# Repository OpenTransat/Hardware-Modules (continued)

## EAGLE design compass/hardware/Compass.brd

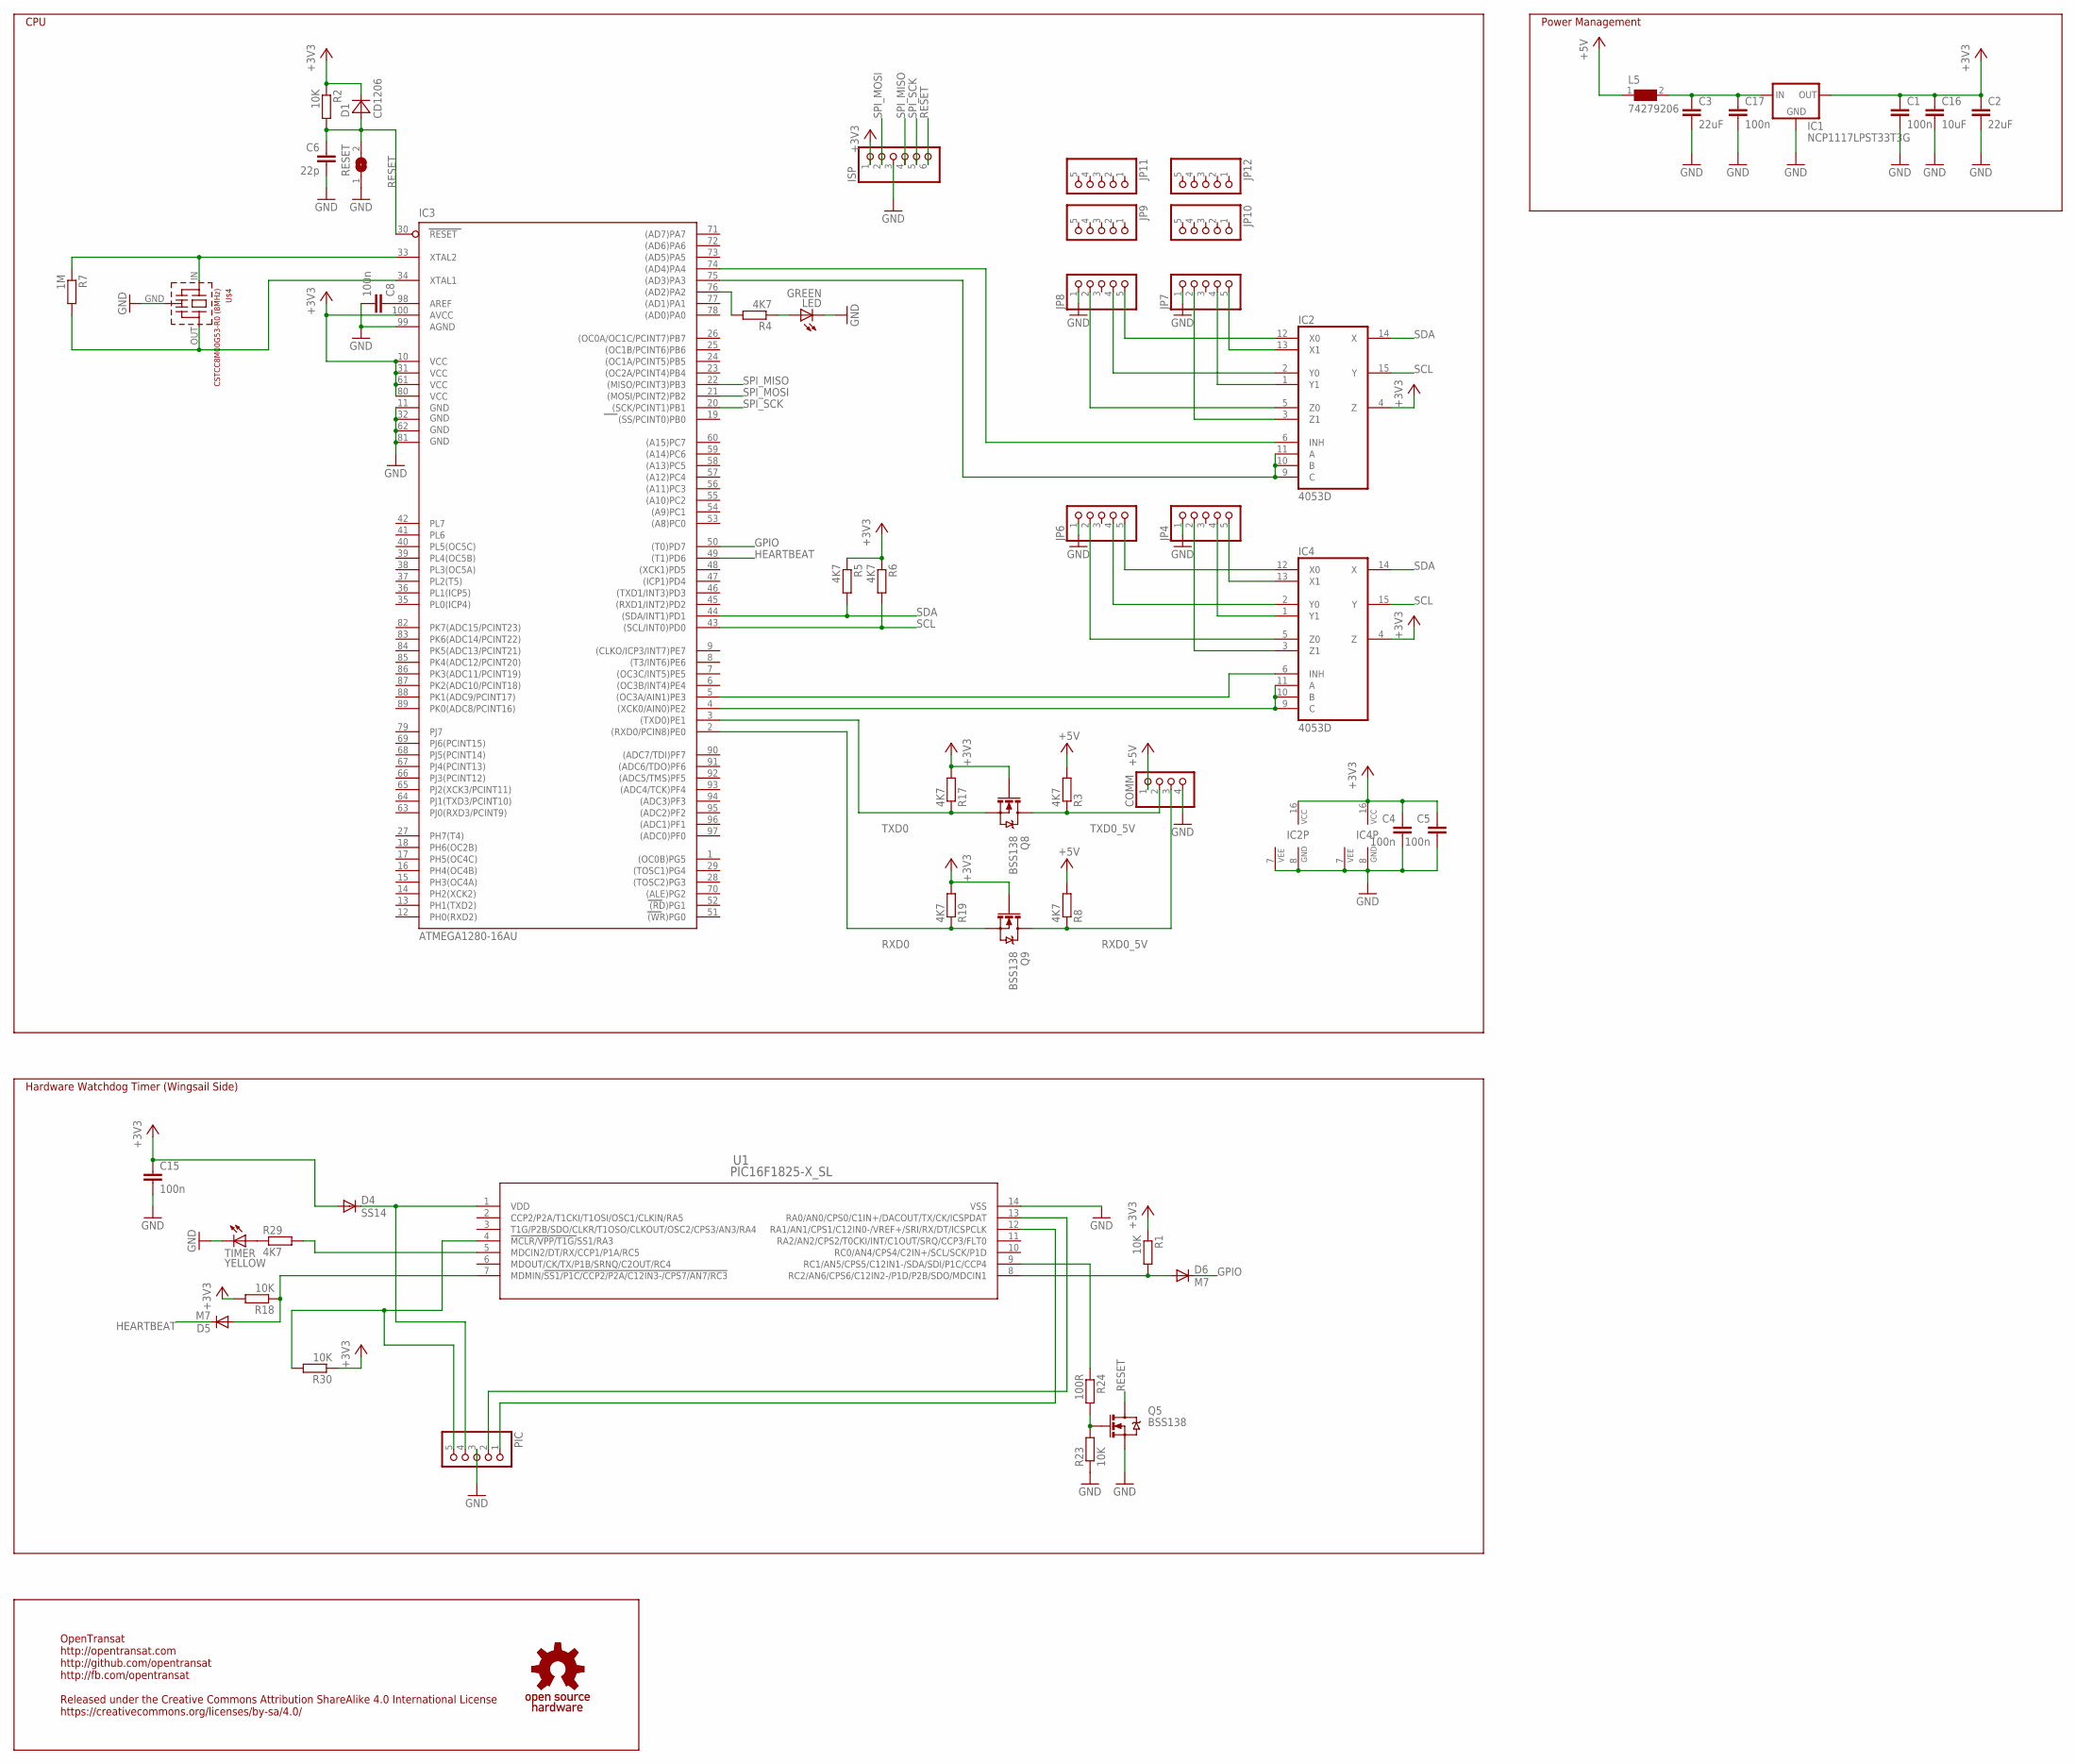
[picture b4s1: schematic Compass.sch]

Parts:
C1, C4, C5, C8, C15, C17: 100n; C0603
C2, C3: 22uF; C1210
C6: 22p; C0603
C16: 10uF; C1206
COMM: PINHD-1X4/90; 1X04/90
D1: CD1206; R1206
D4: SS14; DO214AC
D5, D6: M7; DO-214AC
IC1: NCP1117LPST33T3G; SOT223
IC2, IC4: 4053D; SO16
IC3: ATMEGA1280-16AU; TQFP100
ISP: PINHD-1X6/90; 1X06/90
JP4, JP6, JP7, JP8, JP9, JP10, JP11, JP12: PINHD-1X5; 1X05
L5: 74279206; 0805
LED: GREEN; CHIPLED_0805
PIC: PINHD-1X5/90; 1X05/90
Q5, Q8, Q9: BSS138; SOT23-3
R1, R2, R18, R23, R30: 10K; R0603
R3, R4, R5, R6, R8, R17, R19, R29: 4K7; R0603
R7: 1M; R0603
R24: 100R; R0603
RESET: SJW
TIMER: YELLOW; CHIPLED_0805
U1: PIC16F1825-X_SL; SOIC14-N_MC
U$1: OSHW_S; OSHWS
U$4: CSTCC8M00G53-R0 (8MHz); CSTCC

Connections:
+3V3: C1.1, C2.1, C4.1, C5.1, C15.1, C16.1, D1.2 (C), D4.A, IC1.2 (OUT), IC1.4 (OUT), IC2.4 (Z), IC2.16 (VCC), IC3.10 (VCC), IC3.31 (VCC1), IC3.61 (VCC2), IC3.80 (VCC3), IC3.100 (AVCC), IC4.4 (Z), IC4.16 (VCC), ISP.1, Q8.1 (G), Q9.1 (G), R1.1, R2.1, R5.1, R6.1, R17.2, R18.2, R19.2, R30.1
+5V: COMM.1, L5.1, R3.2, R8.2
GND: C1.2, C2.2, C3.2, C4.2, C5.2, C6.2, C8.2, C15.2, C16.2, C17.2, COMM.4, IC1.1 (GND), IC2.7 (VEE), IC2.8 (GND), IC3.11 (GND), IC3.32 (GND1), IC3.62 (GND2), IC3.81 (GND3), IC3.99 (AGND), IC4.7 (VEE), IC4.8 (GND), ISP.3, JP4.1, JP6.1, JP7.1, JP8.1, LED.C, PIC.3, Q5.2 (S), R23.1, RESET.1, TIMER.C, U1.14 (VSS), U$4.GND
GPIO: D6.C, IC3.50 ((T0)PD7)
HEARTBEAT: D5.C, IC3.49 ((T1)PD6)
unnamed: C3.1, C17.1, IC1.3 (IN), L5.2
unnamed: D6.A, R1.2, U1.8 (RC2/AN6/CPS6/C12IN2-/P1D/P2B/SDO/MDCIN1)
unnamed: C8.1, IC3.98 (AREF)
unnamed: IC4.3 (Z1), JP4.2
unnamed: LED.A, R4.1
unnamed: IC4.1 (Y1), JP4.4
unnamed: IC3.76 ((AD2)PA2), R4.2
unnamed: IC3.4 ((XCK0/AIN0)PE2), IC4.9 (C), IC4.10 (B), IC4.11 (A)
unnamed: IC3.5 ((OC3A/AIN1)PE3), IC4.6 (INH)
unnamed: IC4.13 (X1), JP4.5
unnamed: IC4.12 (X0), JP6.5
unnamed: IC4.2 (Y0), JP6.4
unnamed: IC4.5 (Z0), JP6.2
unnamed: IC2.9 (C), IC2.10 (B), IC2.11 (A), IC3.75 ((AD3)PA3)
unnamed: IC2.6 (INH), IC3.74 ((AD4)PA4)
unnamed: IC2.3 (Z1), JP7.2
unnamed: IC2.1 (Y1), JP7.4
unnamed: IC2.13 (X1), JP7.5
unnamed: IC2.12 (X0), JP8.5
unnamed: IC2.2 (Y0), JP8.4
unnamed: IC2.5 (Z0), JP8.2
unnamed: D5.A, R18.1, U1.7 (MDMIN/!SS1/P1C/CCP2/P2A/C12IN3-/CPS7/AN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)
unnamed: PIC.2, U1.13 (RA0/AN0/CPS0/C1IN+/DACOUT/TX/CK/ICSPDAT)
unnamed: PIC.5, R30.2, U1.4 (!MCLR/VPP/T1G/!SS1/RA3)
unnamed: PIC.1, U1.12 (RA1/AN1/CPS1/C12IN0-/VREF+/SRI/RX/DT/IC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)
unnamed: D4.C, PIC.4, U1.1 (VDD)
unnamed: R24.1, U1.9 (RC1/AN5/CPS5/C12IN1-/SDA/SDI/P1C/CCP4)
unnamed: Q5.1 (G), R23.2, R24.2
unnamed: R29.2, U1.5 (MDCIN2/DT/RX/CCP1/P1A/RC5)
unnamed: R29.1, TIMER.A
RESET: C6.1, D1.1 (A), IC3.30 (RESET), ISP.6, Q5.3 (D), R2.2, RESET.2
RXD0: IC3.2 ((RXD0/PCIN8)PE0), Q9.2 (S), R19.1
RXD0_5V: COMM.3, Q9.3 (D), R8.1
SCL: IC2.15 (Y), IC3.43 ((SCL/INT0)PD0), IC4.15 (Y), R6.2
SDA: IC2.14 (X), IC3.44 ((SDA/INT1)PD1), IC4.14 (X), R5.2
SPI_MISO: IC3.22 ((MISO/PCINT3)PB3), ISP.4
SPI_MOSI: IC3.21 ((MOSI/PCINT2)PB2), ISP.2
SPI_SCK: IC3.20 ((SCK/PCINT1)PB1), ISP.5
TXD0: IC3.3 ((TXD0)PE1), Q8.2 (S), R17.1
TXD0_5V: COMM.2, Q8.3 (D), R3.1
XTAL3: IC3.33 (XTAL2), R7.1, U$4.IN
XTAL4: IC3.34 (XTAL1), R7.2, U$4.OUT

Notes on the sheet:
OpenTransat http://opentransat.com http://github.com/opentransat http://fb.com/opentransat Released under the Creative Commons Attribution ShareAlike 4.0 International License https://creativecommons.org/licenses/by-sa/4.0/
Power Management
CPU
Hardware Watchdog Timer (Wingsail Side)

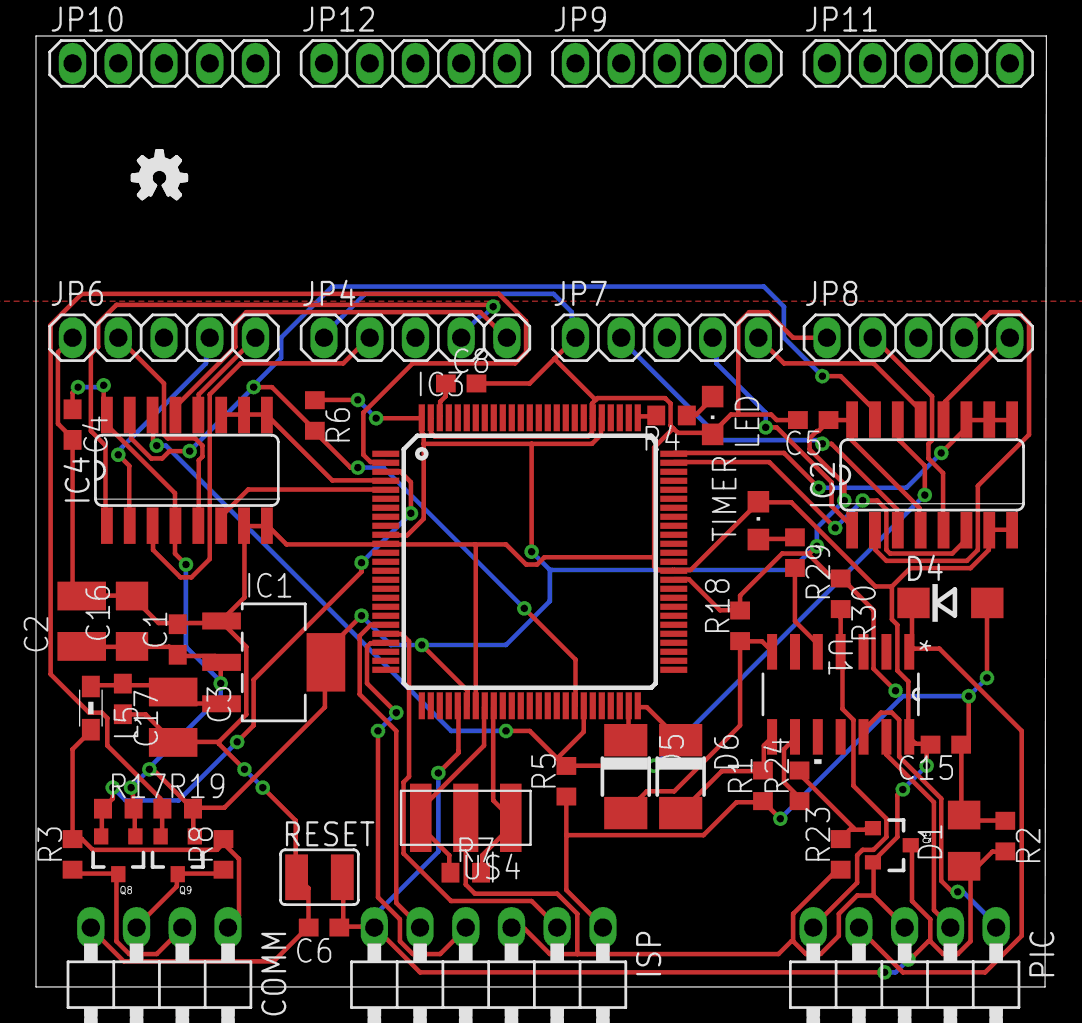
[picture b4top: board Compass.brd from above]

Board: 2 copper layers, 56.1 x 52.8 mm, 54 parts (0 on the bottom side), 47 nets.

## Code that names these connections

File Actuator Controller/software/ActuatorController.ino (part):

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uint8_t buflen = RH_ASK_MAX_MESSAGE_LEN;

//pins
#define LED 13 //PB5
#define HEARTBEAT 6 //PD6
#define IN1 7 //PD7
#define IN2 8 //PB0
#define IN3 9 //PB1
#define IN4 10 //PB2
#define POT A7 //analog input ADC7
#define THERM A0 //analog input PC0,ADC0
#define PWRSENSOR_ON 1 //PD1,TX
#define ACT_ON 0 //PD0,RX (switches EMS & motor driver DC+)
#define RF_TX 3 //PD3
#define RF_RX 2 //PD2
#define RF_TX_ON 5 //PD5
#define RF_RX_ON 4 //PD4
#define ENC_CS A1 //PC1, EMS:6
#define ENC_CLK A3 //PC3, EMS:2
#define ENC_DO A2 //PC2, EMS:4

#define ACT_TIMEOUT 45000UL //number of milliseconds when the actuator is not moving
#define ENC_TRIALS 10 //how many times to read the encoder when parity fails
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void setup() {
  pinMode(LED, OUTPUT);
  digitalWrite(LED, LOW);
  pinMode(HEARTBEAT, OUTPUT);


  #ifdef SERIAL_DEBUG
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  
  pinMode(ACT_ON, OUTPUT);
  digitalWrite(ACT_ON, LOW);
  pinMode(RF_TX_ON, OUTPUT);
  digitalWrite(RF_TX_ON, LOW); //transmitter on only when needed
  pinMode(RF_RX_ON, OUTPUT);
  digitalWrite(RF_RX_ON, LOW);

  ina219.begin(); 
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
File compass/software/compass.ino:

//increase I2C BUFFER to 128 bytes:
//twi.h: TWI_BUFFER_LENGTH 128
//Wire.h: BUFFER_LENGTH 128

#include "Globals.h"
#include <Wire.h>
#include <SPI.h>
#include <EEPROM.h>

#define ROUND(x) ((x)>=0?(int)((x)+0.5):(int)((x)-0.5))
#define RESET() digitalWrite(GPIO, LOW)
#define DELAY_RESET() { delay_sec(4); digitalWrite(GPIO, LOW); }

//#define SERIAL_DEBUG //show command received
//#define DEBUG_COMPASS //uncomment for calibrating
//#define CALIB_COMPASS //uncomment for calibrating

#define DEFAULT_COMPASS 1
#define SERIAL_BAUD 38400 //accepted baud for 8MHz: 9600, 14400, 19200, 38400 https://cache.amobbs.com/bbs_upload782111/files_22/ourdev_508497.html
#define DETECT_CHANGE_EQUAL_MAX 50
#define DETECT_CHANGE_FLOAT_FACTOR 10000

#define LED 24 //PA2
#define MUX1_ABC 70 //PE2
#define MUX1_INH 5 //PE3
#define MUX2_ABC 25 //PA3
#define MUX2_INH 26 //PA4
#define HEARTBEAT 71 //PD6
#define GPIO 38 //PD7

char hb;
bool save_calib = false;

//EEPROM data with checking to store the next waypoint
struct EEPROM_data {
  uint8_t compass_num;
  uint8_t crc;
};
EEPROM_data ee;
#define EEPROM_ADDR 0

void saveEEPROM() {
  ee.crc = ee.compass_num;
  EEPROM.put(EEPROM_ADDR, ee);
}

void loadEEPROM() {
  EEPROM.get(EEPROM_ADDR, ee);
  if (ee.compass_num < 1 || ee.compass_num > 4 || ee.crc != ee.compass_num) {
    ee.compass_num = DEFAULT_COMPASS;
    saveEEPROM();
  }
}

void setCompass(uint8_t x) { //0 = none, 1, 2, 3, 4
  ee.compass_num = x; // global var
  switch (x) {
    case 0:
      digitalWrite(MUX1_INH, HIGH);
      digitalWrite(MUX1_INH, HIGH);
      digitalWrite(MUX1_ABC, LOW);
      digitalWrite(MUX2_ABC, LOW);
      break;
    case 1:
      digitalWrite(MUX2_INH, HIGH);
      digitalWrite(MUX2_ABC, LOW);
      digitalWrite(MUX1_ABC, LOW);
      digitalWrite(MUX1_INH, LOW);
      break;       
    case 2:
      digitalWrite(MUX2_INH, HIGH);
      digitalWrite(MUX2_ABC, LOW);
      digitalWrite(MUX1_ABC, HIGH);    
      digitalWrite(MUX1_INH, LOW);
      break;       
    case 3:
      digitalWrite(MUX1_INH, HIGH);
      digitalWrite(MUX1_ABC, LOW);    
      digitalWrite(MUX2_ABC, HIGH);    
      digitalWrite(MUX2_INH, LOW);
      break;       
    case 4:
      digitalWrite(MUX1_INH, HIGH);
      digitalWrite(MUX1_ABC, LOW);    
      digitalWrite(MUX2_ABC, LOW);    
      digitalWrite(MUX2_INH, LOW);
      break;
    default:
      break;
  }
}

void saveCompass(uint8_t x) {
  ee.compass_num = x;
  saveEEPROM();
}

void setup() {
  //first, all inputs with pullups to minimize power consumption
  DDRA = 0b00000000;
  PORTA = 0b11111111;
  DDRB = 0b00000000;
  PORTB = 0b11111111;
  DDRC = 0b00000000;
  PORTC = 0b11111111;
  DDRD = 0b00000000;
  PORTD = 0b11111111;
  DDRE = 0b00000000;
  PORTE = 0b11111111;
  DDRF = 0b00000000;
  PORTF = 0b11111111;
  DDRG = 0b00000000;
  PORTG = 0b11111111;
  DDRG = 0b00000000;
  PORTG = 0b11111111;
  DDRH = 0b00000000;
  PORTH = 0b11111111;
  DDRJ = 0b00000000;
  PORTJ = 0b11111111;
  DDRK = 0b00000000;
  PORTK = 0b11111111;
  DDRL = 0b00000000;
  PORTL = 0b11111111;
  
  pinMode(MUX1_INH, OUTPUT);
  digitalWrite(MUX1_INH, HIGH); //all compasses turned off by default

  pinMode(MUX2_INH, OUTPUT);
  digitalWrite(MUX2_INH, HIGH); //all compasses turned off by default

  pinMode(MUX1_ABC, OUTPUT);
  pinMode(MUX2_ABC, OUTPUT);

  pinMode(LED, OUTPUT);
  digitalWrite(LED, LOW);

  pinMode(HEARTBEAT, OUTPUT);
  hb = LOW;
  digitalWrite(HEARTBEAT, hb);
  pinMode(GPIO, OUTPUT);
  digitalWrite(GPIO, HIGH);

  Serial.begin(SERIAL_BAUD);
  Serial.println("******************* start *******************");

  loadEEPROM();
  startCompass(ee.compass_num);
}

void startCompass(char cmp) {
  delay_sec(1); //delay to propagate power, otherwise the compass freezes at *warm start*
  readcmd(); //reads command E<num>; from the main controller to change compass and store it in EEPROM
  setCompass(cmp);
  delay_sec(1); //delay to propagate power, otherwise the compass freezes at *warm start*
  Wire.begin();
  initCompass();  
}

void heartbeat() {
  hb = !hb;
  digitalWrite(HEARTBEAT, hb);  
}

void delay_sec(int n) {
  while(n--) {
    delay(1000);
    heartbeat();
  }
}

void fixAHRS() {
  Yaw -= 270.0f;
  if (Yaw < 0) Yaw += 360.0f;
  float p = Pitch;
  Pitch = -Roll;
  Roll = p;
}

void printHuman() {
  Serial.print((uint8_t)ee.compass_num);
  Serial.print(" ");
  Serial.print(Yaw);
  Serial.print(" ");
  Serial.print(Pitch);
  Serial.print(" ");
  Serial.print(Roll);
  Serial.print(" ");
  Serial.println(temperature);
}

void printNMEA() {
  char buf[128];
  char Yaw_str[16];
  dtostrf(Yaw, 0, 4, Yaw_str);
  sprintf(buf, "C,%u,%s,%d,%d,%d", ee.compass_num, Yaw_str, ROUND(Pitch), ROUND(Roll), ROUND(temperature));
  Serial.print("$");
  Serial.print(buf);
  Serial.print('*');
  PrintHex8(checksum(buf));
  Serial.println();
}

void detectChange() {
  static float Yaw_prev = 0;
  static int counter = 0;
  
  if ((long)(Yaw*DETECT_CHANGE_FLOAT_FACTOR) == (long)(Yaw_prev*DETECT_CHANGE_FLOAT_FACTOR))
    counter++;
  else
    counter = 0;

  if (counter > DETECT_CHANGE_EQUAL_MAX)
    DELAY_RESET();

  Yaw_prev = Yaw;
}

void runCompass() {
  #ifdef CALIB_COMPASS
    calibCompass();
    readcmd();
  #else
    readCompass();
    detectChange();
    fixAHRS();
    //printHuman();
    printNMEA();
    smartDelay(100); //read command characters
  #endif  
}

void loop() {
  heartbeat();
  runCompass();
}

void smartDelay(unsigned long ms) {
  unsigned long start = millis();
  do {
    while (Serial.available()) {
      readcmd();
    }
  } while (millis() - start < ms);
}

void blinkN(char n) {
  while(n--) {
    digitalWrite(LED, HIGH);
    delay(200);
    digitalWrite(LED, LOW);
    delay(200);
  }
  delay_sec(2);
}

void compass_power_test() {
  setCompass(1);
  blinkN(1);
  setCompass(2);
  blinkN(2);
  setCompass(3);
  blinkN(3);
  setCompass(4);
  blinkN(4);
  blinkN(5);
  RESET();
  blinkN(6);
  blinkN(7);
}

////////////////////////////////////////////////////////////

String cmd = "";
int cmdlen;
#define cmdmax 200

void readcmd() {
  while (Serial.available() > 0) {
    char ch = (char)Serial.read();
    if (ch == '\n' || ch == '\r') continue;
    if (ch == 'S')
      save_calib = true;      
    if (ch == ';') { //end of command, process
      execmd();
      cmd = "";
      cmdlen = 0;
    }
    else if (ch == '$') { //start a new command (optional)
      cmd = "";
      cmdlen = 0;
    }
    else {
      cmd += ch;
      cmdlen++;
    }
    if (cmdlen > cmdmax-2) { //too long command
      cmd = "";
      cmdlen = 0;      
    }
  }
}

void execmd() {
  #ifdef SERIAL_DEBUG
    Serial.print("COMMAND: "); Serial.println(cmd);
  #endif
  //find first digit
  int i = 0;
  while(i < cmd.length() && !isDigit(cmd[i]) && cmd[i] != '-') i++;
  //
  String cmd1 = cmd.substring(0, i);
  String cmd2_str = cmd.substring(i);
  int cmd2 = cmd2_str.toInt();
  if (cmd1 == "C" && cmd2 >= 0 && cmd2 <= 4) { //set compass
    startCompass(cmd2);
  }
  if (cmd1 == "E" && cmd2 >= 0 && cmd2 <= 4) { //change compass, store it in EEPROM and reset
    if (cmd2 != ee.compass_num) {
      saveCompass(cmd2);
      delay_sec(1);
      RESET();
    }
  }
  if (cmd1 == "RESET" && cmd2 == 0) { //reset
    delay_sec(1);
    RESET();
  }
}

//////////////////////////////////////////////////////

unsigned char checksum(char* s) {
  unsigned char ret = 0;
  while (*s != '\0') {
    ret ^= *s;
    s++;
  }
  return ret;
}

void PrintHex8(char X) {
  if (X < 16)
    Serial.print("0");
  Serial.print(X, HEX);
}

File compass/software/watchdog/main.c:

/*
Hardware watchdog timer based on PIC16F1825

OpenTransat
http://opentransat.com
http://github.com/opentransat
http://fb.com/opentransat

Released under the Creative Commons Attribution ShareAlike 4.0 International License
https://creativecommons.org/licenses/by-sa/4.0/
*/

#define _XTAL_FREQ 31000UL
#include "config.h"
#include <xc.h>

#define NAVRESET PORTCbits.RC1
#define GPIO PORTCbits.RC2
#define HEARTBEAT PORTCbits.RC3
#define LED PORTCbits.RC5

#define TMR1_MAX 7750 //timer1 increment after 4 seconds: 31000 / 4 / 8 * #seconds

void init_io() {
    OSCCONbits.IRCF = 0b0000; //31kHz oscillator
    TRISA = 0;
    PORTA = 0;
    TRISC = 0b00001100; //RC1 = NAVRESET (active high), RC2 = GPIO (input), RC3 = HARTBEAT (input), RC5 = LED (active high)
    PORTC = 0b00000000;
  
    //timer1 for detecting heartbeat
    T1CONbits.TMR1CS = 0b00; //increment on Fosc/4
    T1CONbits.T1CKPS = 0b11; //prescaler 1:8
    TMR1ON = 1;

    //disable all analog ports
    ANSELA = 0;
    ANSELC = 0;

    //disable some peripherals
    CM1CON0bits.C1ON = 0;
    CM2CON0bits.C2ON = 0;
    RCSTAbits.SPEN = 0;    
}

void delay_sec(unsigned int n) {
    while (n--) {
        CLRWDT();
        LED = LED?0:1;
        __delay_ms(1000);
    }
}

void navreset() {
    NAVRESET = 1;
    __delay_us(200);    
    NAVRESET = 0;
}

void main(void) {
    char hb, hb_prev;

    init_io();

    TMR1 = 0;
    
    while(1) {
        CLRWDT();
        hb = HEARTBEAT;

        if (hb != hb_prev) { //reset timer
            TMR1 = 0;
            LED = 1;
            __delay_ms(10);
            LED = 0;
        }
        
        if (TMR1 > TMR1_MAX || !GPIO) { //reset master CPU
            navreset();
            TMR1 = 0;
            LED = 1;
            __delay_ms(10);
            LED = 0;
        }
        
        hb_prev = hb;
    }
    return;
}

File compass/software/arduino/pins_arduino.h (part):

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#define digitalPinHasPWM(p)         (((p) >= 2 && (p) <= 13) || ((p) >= 44 && (p)<= 46))

#define PIN_SPI_SS    (53)
#define PIN_SPI_MOSI  (51)
#define PIN_SPI_MISO  (50)
#define PIN_SPI_SCK   (52)

static const uint8_t SS   = PIN_SPI_SS;
static const uint8_t MOSI = PIN_SPI_MOSI;
static const uint8_t MISO = PIN_SPI_MISO;
static const uint8_t SCK  = PIN_SPI_SCK;

#define PIN_WIRE_SDA        (20)
#define PIN_WIRE_SCL        (21)
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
